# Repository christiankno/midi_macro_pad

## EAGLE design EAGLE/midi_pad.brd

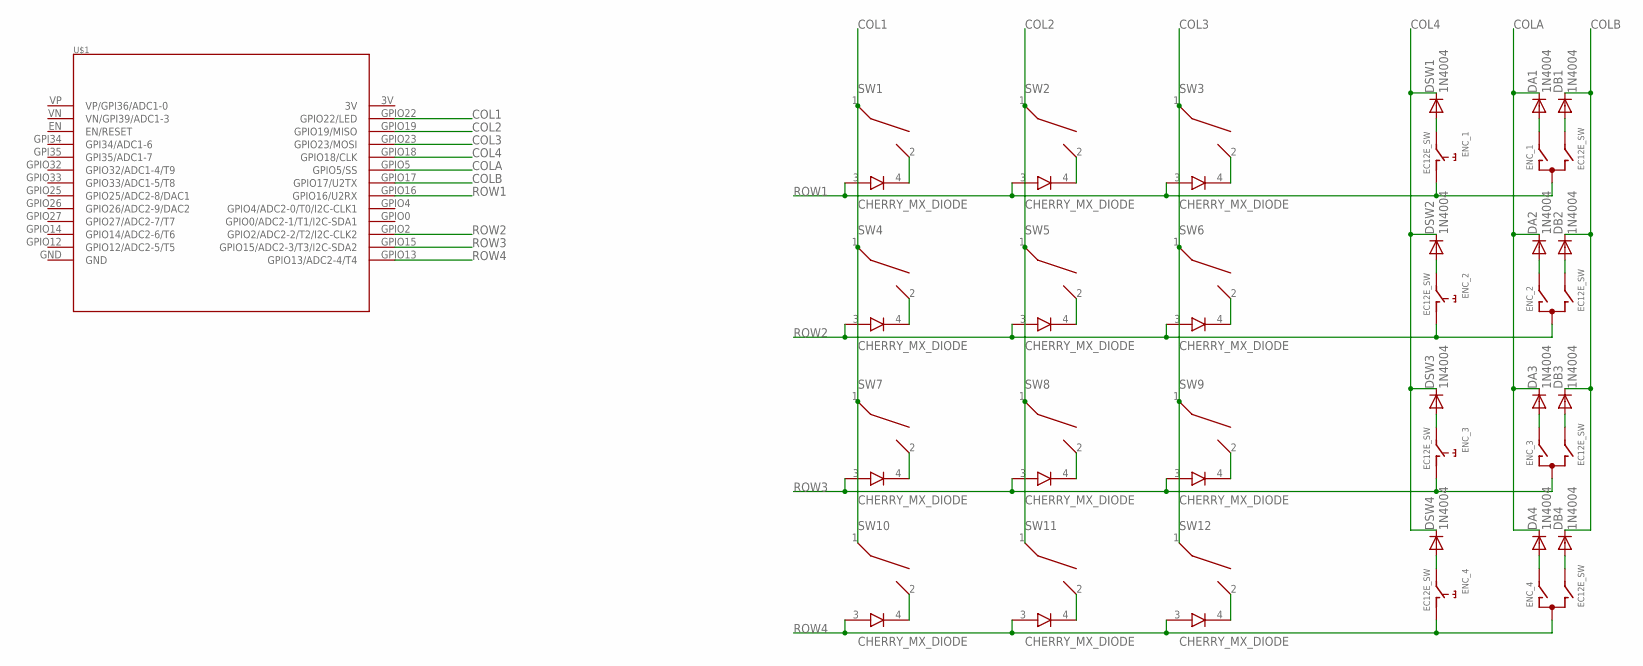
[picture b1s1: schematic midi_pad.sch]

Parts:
DA1, DA2, DA3, DA4: 1N4004; DO41-10
DB1, DB2, DB3, DB4: 1N4004; DO41-10
DSW1, DSW2, DSW3, DSW4: 1N4004; DO41-10
ENC_1, ENC_2, ENC_3, ENC_4: EC12E_SW; ALPS_EC12E_SW
SW1, SW2, SW3, SW4, SW5, SW6, SW7, SW8, SW9, SW10, SW11, SW12: CHERRY_MX_DIODE; MX1A-XX[D/J]N
U$1: LOLIN32_LITE

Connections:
COL1: SW1.1, SW4.1, SW7.1, SW10.1, U$1.GPIO22 (GPIO22/LED)
COL2: SW2.1, SW5.1, SW8.1, SW11.1, U$1.GPIO19 (GPIO19/MISO)
COL3: SW3.1, SW6.1, SW9.1, SW12.1, U$1.GPIO23 (GPIO23/MOSI)
COL4: DSW1.C, DSW2.C, DSW3.C, DSW4.C, U$1.GPIO18 (GPIO18/CLK)
COLA: DA1.C, DA2.C, DA3.C, DA4.C, U$1.GPIO5 (GPIO5/SS)
COLB: DB1.C, DB2.C, DB3.C, DB4.C, U$1.GPIO17 (GPIO17/U2TX)
unnamed: SW1.2, SW1.4
unnamed: SW2.2, SW2.4
unnamed: SW3.2, SW3.4
unnamed: SW4.2, SW4.4
unnamed: SW5.2, SW5.4
unnamed: SW6.2, SW6.4
unnamed: SW7.2, SW7.4
unnamed: SW8.2, SW8.4
unnamed: SW9.2, SW9.4
unnamed: SW10.2, SW10.4
unnamed: SW11.2, SW11.4
unnamed: SW12.2, SW12.4
unnamed: DSW1.A, ENC_1.E (2)
unnamed: DA1.A, ENC_1.A
unnamed: DB1.A, ENC_1.B
unnamed: DSW2.A, ENC_2.E (2)
unnamed: DA2.A, ENC_2.A
unnamed: DB2.A, ENC_2.B
unnamed: DSW3.A, ENC_3.E (2)
unnamed: DA3.A, ENC_3.A
unnamed: DB3.A, ENC_3.B
unnamed: DSW4.A, ENC_4.E (2)
unnamed: DA4.A, ENC_4.A
unnamed: DB4.A, ENC_4.B
ROW1: ENC_1.C, ENC_1.D (1), SW1.3, SW2.3, SW3.3, U$1.GPIO16 (GPIO16/U2RX)
ROW2: ENC_2.C, ENC_2.D (1), SW4.3, SW5.3, SW6.3, U$1.GPIO2 (GPIO2/ADC2-2/T2/I2C-CLK2)
ROW3: ENC_3.C, ENC_3.D (1), SW7.3, SW8.3, SW9.3, U$1.GPIO15 (GPIO15/ADC2-3/T3/I2C-SDA2)
ROW4: ENC_4.C, ENC_4.D (1), SW10.3, SW11.3, SW12.3, U$1.GPIO13 (GPIO13/ADC2-4/T4)

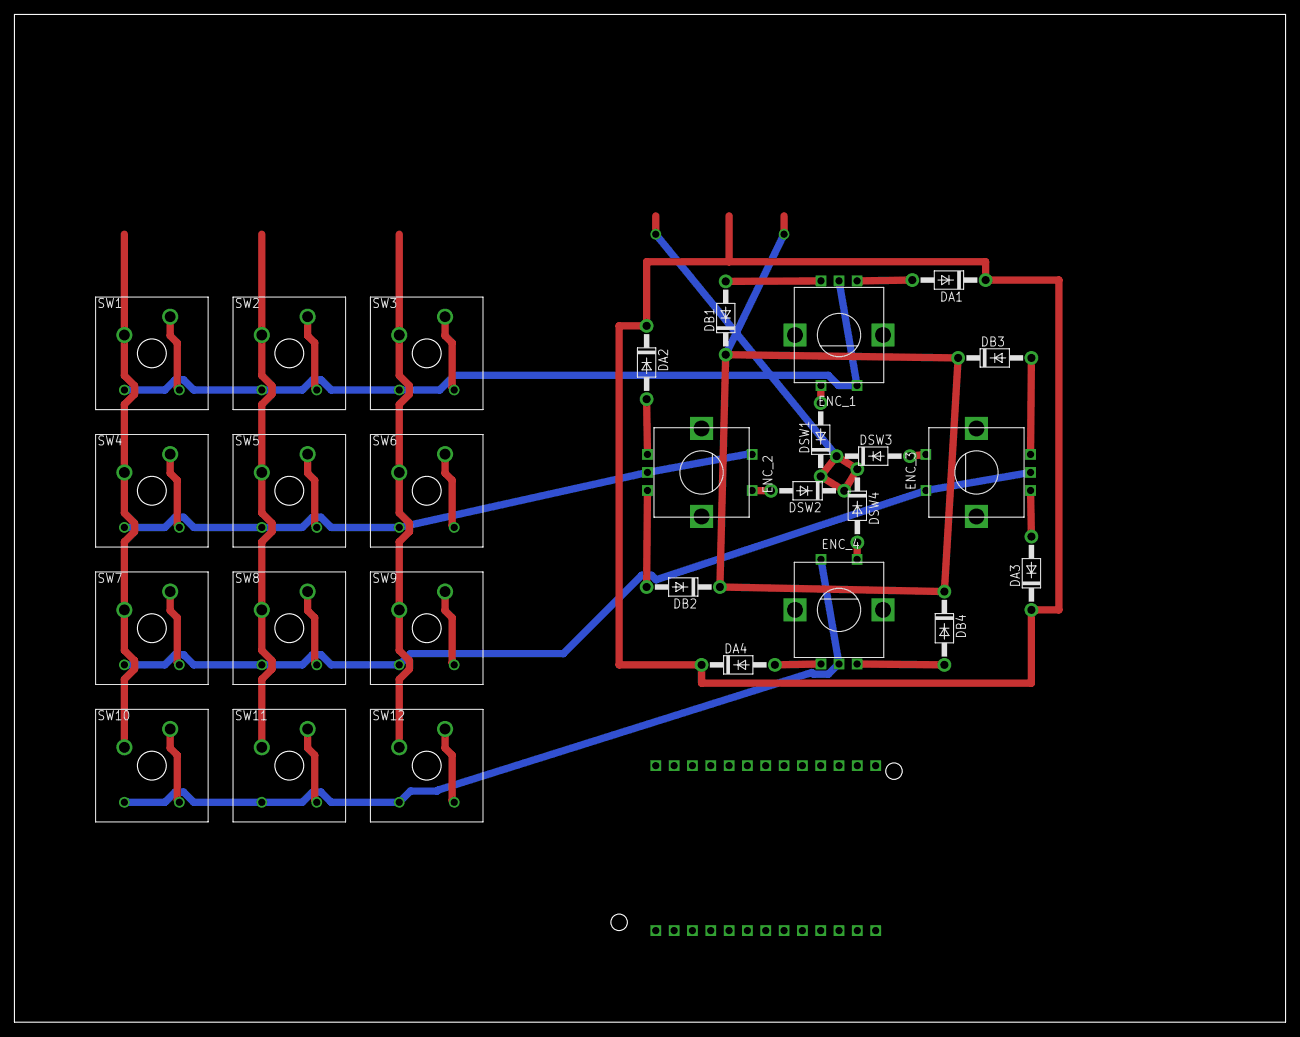
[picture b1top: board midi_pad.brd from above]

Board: 2 copper layers, 176.2 x 139.7 mm, 29 parts (0 on the bottom side), 34 nets.

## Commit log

2022-09-26 Completed support for matrix inputs
2023-02-24 Moved files around to be cleaner
2023-02-25 inclusion of other project files
